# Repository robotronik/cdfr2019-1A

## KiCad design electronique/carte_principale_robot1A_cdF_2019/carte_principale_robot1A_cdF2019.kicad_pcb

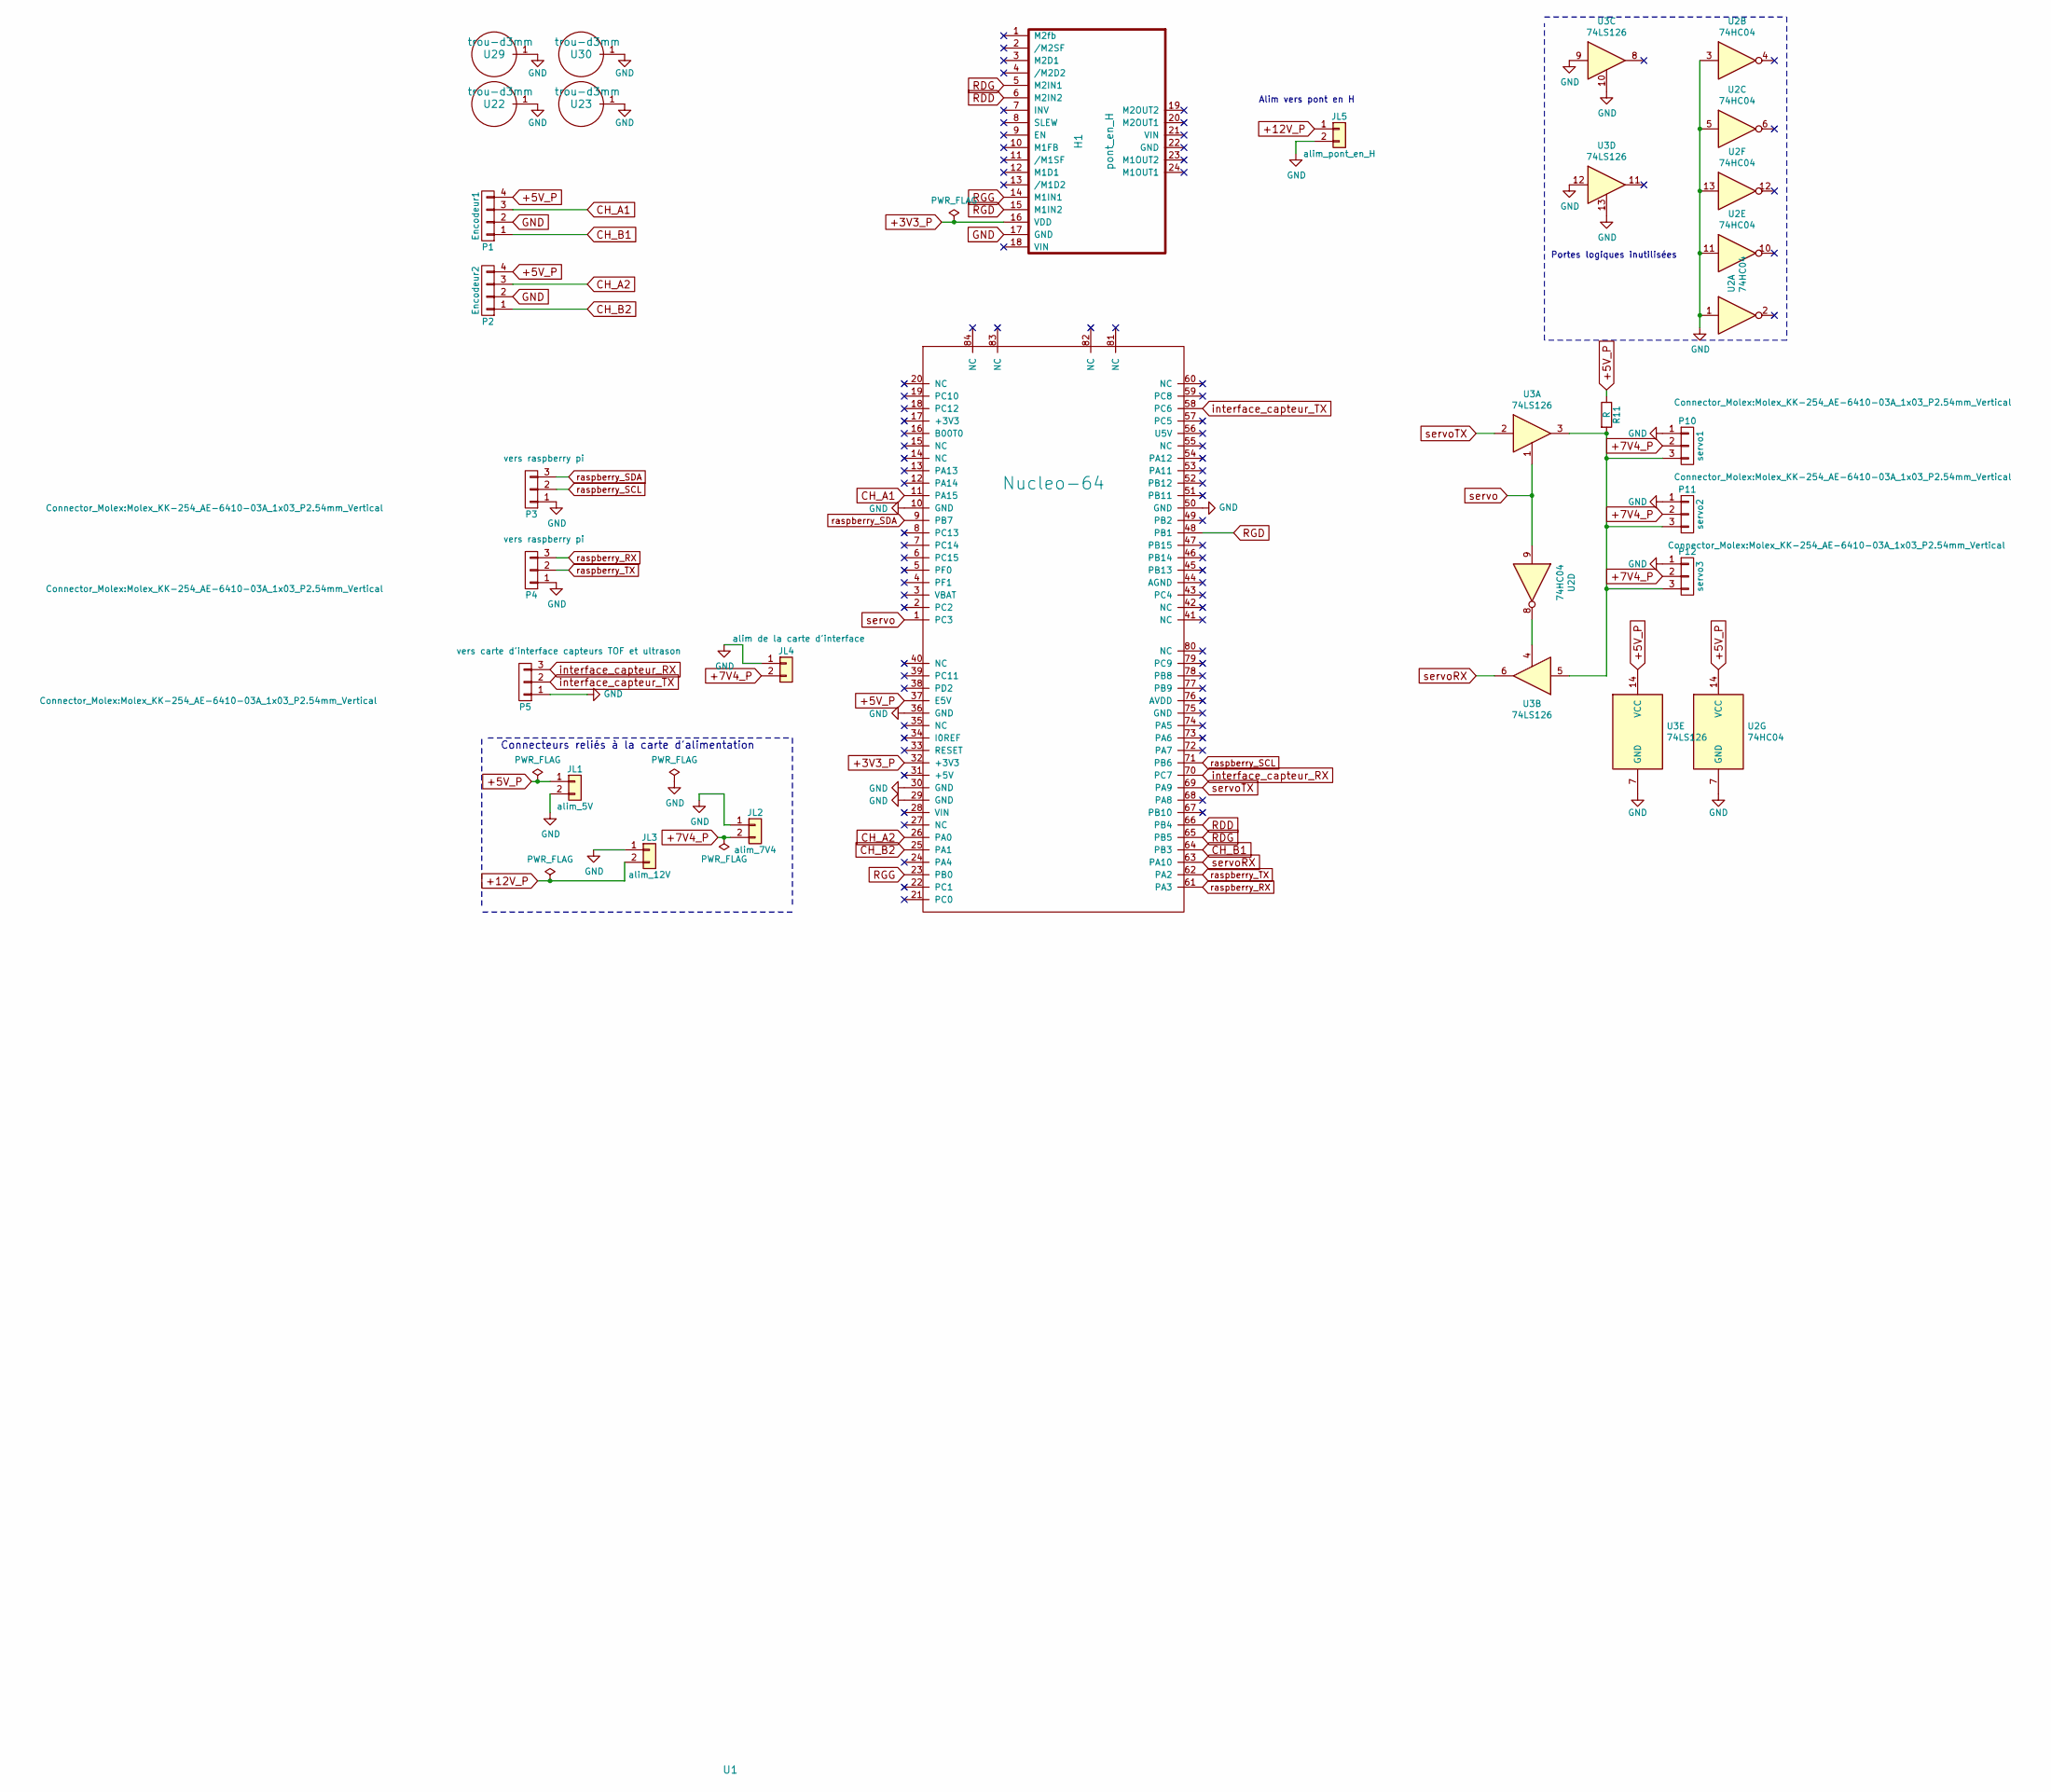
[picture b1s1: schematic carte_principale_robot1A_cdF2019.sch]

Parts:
H1: pont_en_H; MC33926-Pont en H
JL1: alim_5V; Molex_KK-254_AE-6410-02A_1x02_P2.54mm_Vertical
JL2: alim_7V4; B plug 5mm
JL3: alim_12V; B plug 5mm
JL4: alim de la carte d'interface; B plug 5mm
JL5: alim_pont_en_H; PinHeader_1x02_P2.54mm_Vertical
P1: Encodeur1; Molex_KK-254_AE-6410-04A_1x04_P2.54mm_Vertical
P2: Encodeur2; Molex_KK-254_AE-6410-04A_1x04_P2.54mm_Vertical
P3, P4: vers raspberry pi; Molex_KK-254_AE-6410-03A_1x03_P2.54mm_Vertical
P5: vers carte d'interface capteurs TOF et ultrason; Molex_KK-254_AE-6410-03A_1x03_P2.54mm_Vertical
P10: servo1; Molex_KK-254_AE-6410-03A_1x03_P2.54mm_Vertical
P11: servo2; Molex_KK-254_AE-6410-03A_1x03_P2.54mm_Vertical
P12: servo3; Molex_KK-254_AE-6410-03A_1x03_P2.54mm_Vertical
R11: R; R_1206_3216Metric
U1: Nucleo-64
U2: 74HC04; DIP-14_W7.62mm
U3: 74LS126; DIP-14_W7.62mm
U22, U23, U29, U30: trou-d3mm; trou_d3mm

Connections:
+3V3_P: H1.16 (VDD), U1.32 (+3V3)
+5V_P: JL1.1, P1.4, P2.4, R11.1, U1.37 (E5V), U2.14 (VCC), U3.14 (VCC)
+7V4_P: JL2.2, JL4.2, P10.2, P11.2, P12.2
+12V_P: JL3.2, JL5.1
CH_A1: P1.3, U1.11 (PA15)
CH_A2: P2.3, U1.26 (PA0)
CH_B1: P1.1, U1.64 (PB3)
CH_B2: P2.1, U1.25 (PA1)
GND: H1.17 (GND), JL1.2, JL2.1, JL3.1, JL4.1, JL5.2, P1.2, P2.2, P3.1, P4.1, P5.1, P10.1, P11.1, P12.1, U1.10 (GND), U1.29 (GND), U1.30 (GND), U1.36 (GND), U1.50 (GND), U2.1, U2.3, U2.5, U2.7 (GND), U2.11, U2.13, U3.7 (GND), U3.9, U3.10, U3.12, U3.13, U22.1, U23.1, U29.1, U30.1
unnamed: P10.3, P11.3, P12.3, R11.2, U3.3, U3.5
unnamed: U2.8, U3.4
RDD: H1.6 (M2IN2), U1.66 (PB4)
RDG: H1.5 (M2IN1), U1.65 (PB5)
RGD: H1.15 (M1IN2), U1.48 (PB1)
RGG: H1.14 (M1IN1), U1.23 (PB0)
interface_capteur_RX: P5.3, U1.70 (PC7)
interface_capteur_TX: P5.2, U1.58 (PC6)
raspberry_RX: P4.3, U1.61 (PA3)
raspberry_SCL: P3.2, U1.71 (PB6)
raspberry_SDA: P3.3, U1.9 (PB7)
raspberry_TX: P4.2, U1.62 (PA2)
servo: U1.1 (PC3), U2.9, U3.1
servoRX: U1.63 (PA10), U3.6
servoTX: U1.69 (PA9), U3.2

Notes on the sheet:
Connecteurs reliés à la carte d'alimentation
Alim vers pont en H
Portes logiques inutilisées

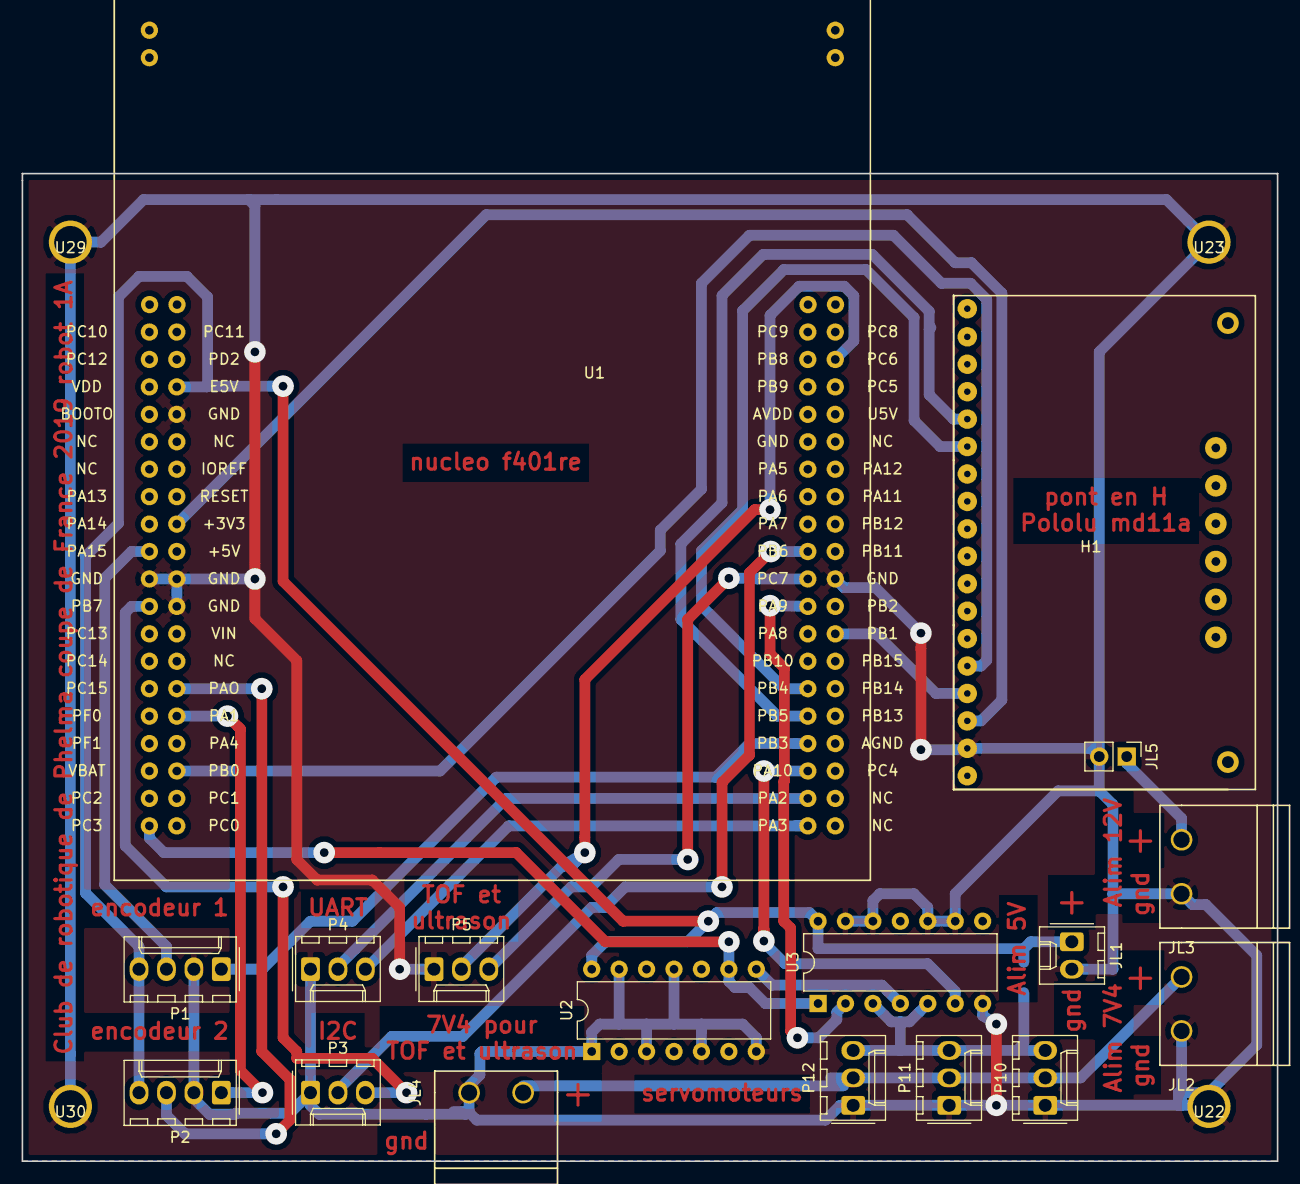
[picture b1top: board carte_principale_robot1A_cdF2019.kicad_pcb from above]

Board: 2 copper layers, 116.2 x 91.4 mm, 22 parts (1 on the bottom side), 24 nets.

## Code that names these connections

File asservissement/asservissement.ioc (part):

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Mcu.Name=STM32F401R(D-E)Tx
Mcu.Package=LQFP64
Mcu.UserName=STM32F401RETx
PA0-WKUP.GPIOParameters=GPIO_PuPd
PA0-WKUP.GPIO_PuPd=GPIO_PULLUP
PA0-WKUP.Signal=S_TIM5_CH1
PA1.GPIOParameters=GPIO_PuPd
PA1.GPIO_PuPd=GPIO_PULLUP
PA1.Signal=S_TIM5_CH2
PA14.Signal=SYS_JTCK-SWCLK
PA15.GPIOParameters=GPIO_PuPd
PA15.GPIO_PuPd=GPIO_PULLUP
PA15.Signal=S_TIM2_CH1_ETR
PA2.Mode=Synchronous
PA2.Signal=USART2_TX
PA3.Mode=Synchronous
PA3.Signal=USART2_RX
PA4.Mode=Synchronous
PA4.Signal=USART2_CK
PB0.Signal=S_TIM3_CH3
PB1.Signal=S_TIM3_CH4
PB3.GPIOParameters=GPIO_ModeDefaultPP,GPIO_PuPd
PB3.GPIO_ModeDefaultPP=GPIO_MODE_AF_PP
PB3.GPIO_PuPd=GPIO_PULLUP
PB3.Signal=S_TIM2_CH2
PB4.Signal=S_TIM3_CH1
PB5.Signal=S_TIM3_CH2
RCC.HSE_VALUE=25000000
RCC.SYSCLKFreq_VALUE=84000000
RCC.SYSCLKSource=RCC_SYSCLKSOURCE_PLLCLK
board=custom

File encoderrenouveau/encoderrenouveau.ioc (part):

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Mcu.Name=STM32F401R(D-E)Tx
Mcu.Package=LQFP64
Mcu.UserName=STM32F401RETx
PA15.GPIOParameters=GPIO_PuPd
PA15.GPIO_PuPd=GPIO_PULLUP
PA15.Signal=S_TIM2_CH1_ETR
PA2.Mode=Synchronous
PA2.Signal=USART2_TX
PA3.Mode=Synchronous
PA3.Signal=USART2_RX
PA4.Mode=Synchronous
PA4.Signal=USART2_CK
PB3.GPIOParameters=GPIO_PuPd
PB3.GPIO_PuPd=GPIO_PULLUP
PB3.Signal=S_TIM2_CH2
PC6.Mode=Synchronous
PC6.Signal=USART6_TX
PC7.Mode=Synchronous
PC7.Signal=USART6_RX
PC8.Mode=Synchronous
PC8.Signal=USART6_CK
RCC.HSE_VALUE=25000000
RCC.SYSCLKFreq_VALUE=84000000
RCC.SYSCLKSource=RCC_SYSCLKSOURCE_PLLCLK
board=custom

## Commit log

2019-03-14 code reseau
2019-03-18 wifi connect
2019-03-20 La carte principale telle qu'elle a été imprimée
2019-03-20 Utile pour la programmation de la carte Nucleo
2019-05-16 travail sur les IC
2019-05-16 code US
2019-05-21 les codes de victor pour les 1A
2019-05-29 update US
    encapsulation dans une fonction
2019-05-30 ftfty
2019-05-30 presque
2019-05-30 enfin
